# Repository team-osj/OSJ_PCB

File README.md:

# PCB Data for OSJ Project
## Specification
### Current Sensing Board
* Power Input - AC 90&#126;240V 50&#126;60HZ
* Main MCU - Atmel Atmega328 With Arduino Bootloader
* Current Sensor - Allegro ACS712 Hall Effect Sensor
* Communication - Nordic NRF24L01 2.4Ghz
### Gateway Board
* Power Input - DC 5V 2A
* Main MCU - Espressif ESP32-WROOM-32U
* Communication - WIFI 802.11 B,G,N   
                  Nordic NRF24L01 2.4Ghz
## Image
### Current Sensing Board TOP

### Current Sensing Board BOTTOM

### Gateway Board TOP

### Gateway Board BOTTOM

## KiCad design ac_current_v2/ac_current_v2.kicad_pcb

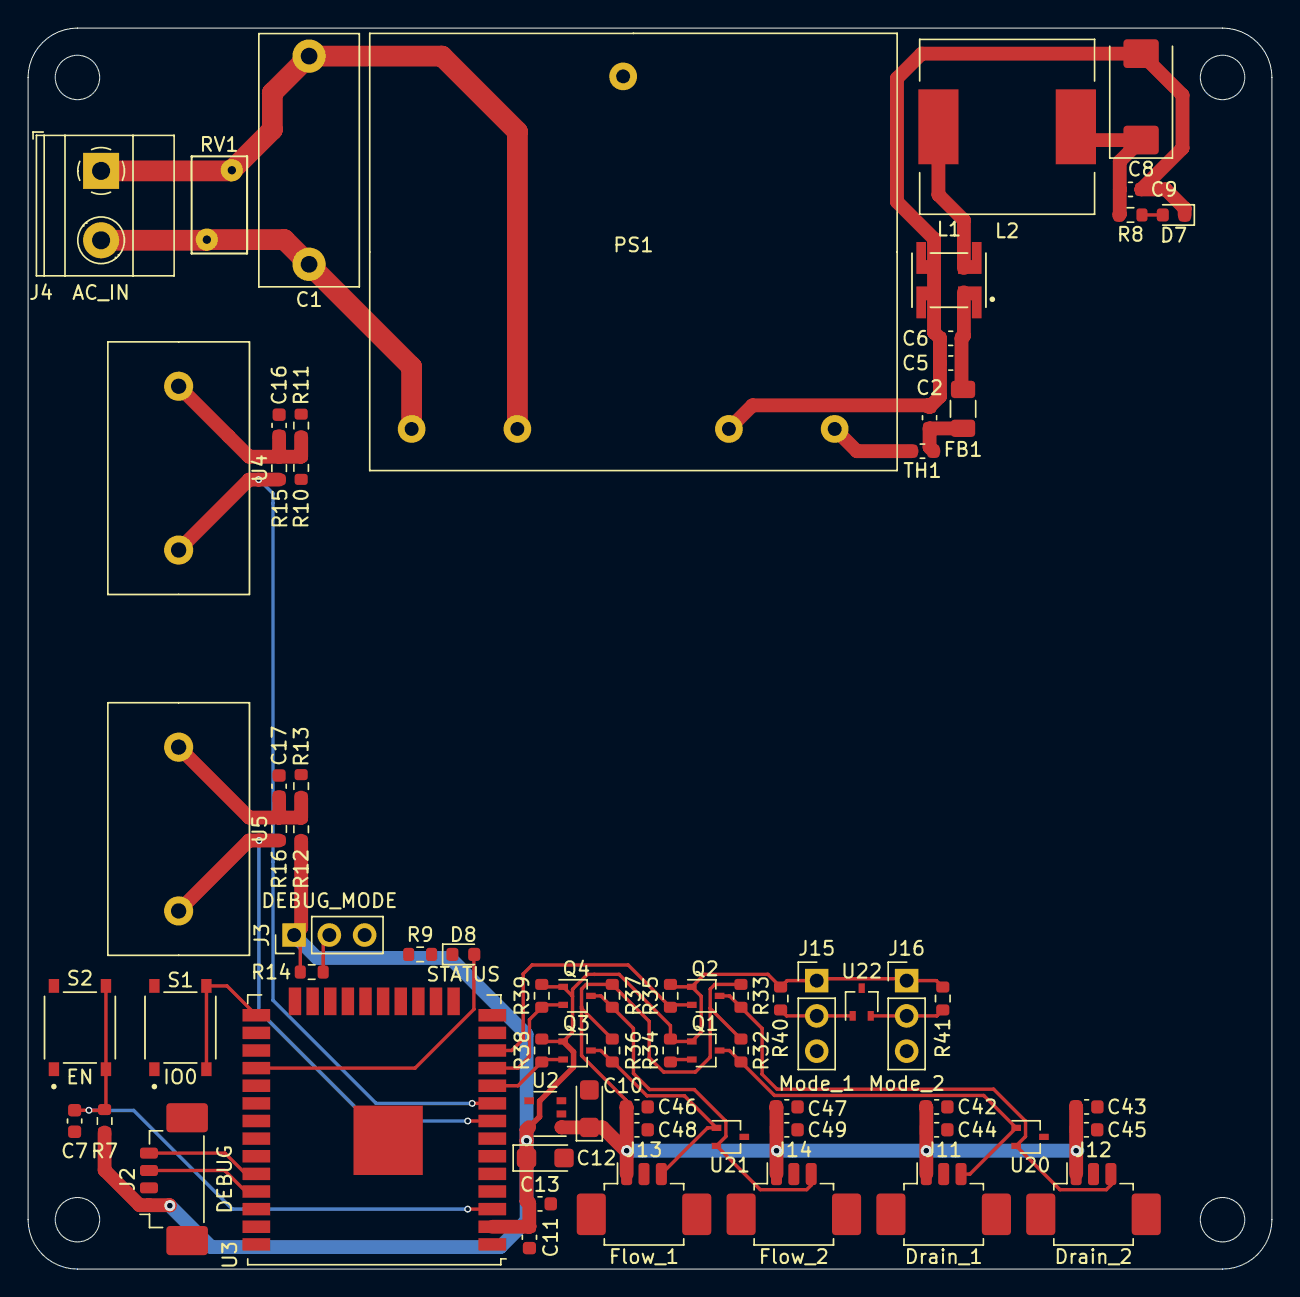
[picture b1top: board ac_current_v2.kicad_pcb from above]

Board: 2 copper layers, 89.6 x 89.4 mm, 75 parts (0 on the bottom side), 31 nets.

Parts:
C1: MPB224K27DZKN158G0; C_Rect_L18.0mm_W7.0mm_P15.00mm_FKS3_FKP3
C2: 10nf; C_0603_1608Metric
C5, C7, C9, C11: 100nf; C_0603_1608Metric
C6, C13, C16, C17, C42, C43, C46, C47: 10uf; C_0603_1608Metric
C8: 330uf; CP_EIA-7343-31_Kemet-D
C10, C12: 10uf; CP_EIA-3216-18_Kemet-A
C44, C45, C48, C49: 100uf; C_0603_1608Metric
D7: 5V; LED_0603_1608Metric
D8: STATUS; LED_0603_1608Metric
FB1: FBMH3216HM221NTV; Fuse_1206_3216Metric
H1, H2, H3, H4: MountingHole_Pad; MountingHole_3.2mm_M3
J2: DEBUG; Molex_PicoBlade_53398-0471_1x04-1MP_P1.25mm_Vertical
J3: DEBUG_MODE; PinHeader_1x03_P2.54mm_Vertical
J4: AC_IN; TerminalBlock_Phoenix_MKDS-1,5-2_1x02_P5.00mm_Horizontal
J11: Drain_1; Molex_PicoBlade_53261-0371_1x03-1MP_P1.25mm_Horizontal
J12: Drain_2; Molex_PicoBlade_53261-0371_1x03-1MP_P1.25mm_Horizontal
J13: Flow_1; Molex_PicoBlade_53261-0371_1x03-1MP_P1.25mm_Horizontal
J14: Flow_2; Molex_PicoBlade_53261-0371_1x03-1MP_P1.25mm_Horizontal
J15: Mode_1; PinHeader_1x03_P2.54mm_Vertical
J16: Mode_2; PinHeader_1x03_P2.54mm_Vertical
L1: DLW5ATN331MQ2L; FIL_DLW5ATN331MQ2L
L2: SCDS125T-220M-N; L_12x12mm_H6mm
PS1: GMS0505
Q1, Q2, Q3, Q4: 2N7002; SOT-323_SC-70
R7, R14, R32, R33, R34, R35, R36, R37, R38, R39, R40, R41: 10k; R_0603_1608Metric
R8: 330; R_0603_1608Metric
R9: 100; R_0603_1608Metric
R10, R11, R12, R13: 100k; R_0603_1608Metric
R15, R16: 33; R_0603_1608Metric
RV1: V07E230P; RV_Disc_D7mm_W4mm_P5mm
S1: IO0; SW_TS-1187A-B-A-B
S2: EN; SW_TS-1187A-B-A-B
TH1: BSMD0603-050-6V; Fuse_0603_1608Metric
U2: NCP603SN330; TSOP-5_1.65x3.05mm_P0.95mm
U3: ESP32-WROOM-32U
U4: CT_1; ZMCT103C
U5: CT_2; ZMCT103C
U20, U21, U22: TPD2E007; SOT-323_SC-70

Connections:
+3V3: C11.2, C12.1, C13.2, J2.1, J3.1, J15.1, J16.1, Q1.1, Q2.1, Q3.1, Q4.1, R7.1, R10.1, R12.1, R14.1, R34.2, R35.2, R38.2, R39.2, R40.2, R41.2, U2.5, U3.2
+5V: C8.1, C9.1, C10.1, C42.1, C43.1, C44.1, C45.1, C46.1, C47.1, C48.1, C49.1, J11.1, J12.1, J13.1, J14.1, L2.2, R8.1, R32.2, R33.2, R36.2, R37.2, U2.1
/CT_1: R15.2, U3.9, U4.1
/CT_2: R16.2, U3.8, U5.1
/Debug_SW: J3.2, R14.2, U3.36
/Drain_1: Q1.2, R34.1, U3.37
/Drain_2: Q2.2, R35.1, U3.12
/EN: C7.1, R7.2, S2.C, S2.D, U3.3
/Flow_1: Q3.2, R38.1, U3.10
/Flow_2: Q4.2, R39.1, U3.11
/IO0: S1.C, S1.D, U3.25
/RX_DEBUG: J2.4, U3.34
/STATUS: D8.2, U3.28
/Sheet65BE28DA/Drain_1: J11.3, Q1.3, R32.1, U20.1
/Sheet65BE28DA/Drain_2: J12.3, Q2.3, R33.1, U20.2
/Sheet65BE28DA/Flow_1: J13.3, Q3.3, R36.1, U21.1
/Sheet65BE28DA/Flow_2: J14.3, Q4.3, R37.1, U21.2
/Sheet65BE28DA/Mode_1: J15.2, R40.1, U22.1
/Sheet65BE28DA/Mode_2: J16.2, R41.1, U22.2
/TX_DEBUG: J2.3, U3.35
GND: C2.2, C5.2, C6.2, C7.2, C8.2, C9.2, C10.2, C11.1, C12.2, C13.1, C16.2, C17.2, C42.2, C43.2, C44.2, C45.2, C46.2, C47.2, C48.2, C49.2, D7.1, J2.2, J3.3, J11.2, J12.2, J13.2, J14.2, J15.3, J16.3, L1.3, L1.4, PS1.3, R9.1, R11.2, R13.2, S1.A, S1.B, S2.A, S2.B, U2.2, U3.1, U3.15, U3.38, U3.39, U20.3, U21.3, U22.3
LINE: C1.1, J4.2, PS1.1, RV1.1
NEUT: C1.2, J4.1, PS1.2, RV1.2
unnamed: C2.1, FB1.2, TH1.1
unnamed: C5.1, C6.1, FB1.1, L1.1
unnamed: C16.1, R10.2, R11.1, R15.1, U4.2
unnamed: C17.1, R12.2, R13.1, R16.1, U5.2
unnamed: D7.2, R8.2
unnamed: D8.1, R9.2
unnamed: L1.2, L2.1
unnamed: PS1.4, TH1.2

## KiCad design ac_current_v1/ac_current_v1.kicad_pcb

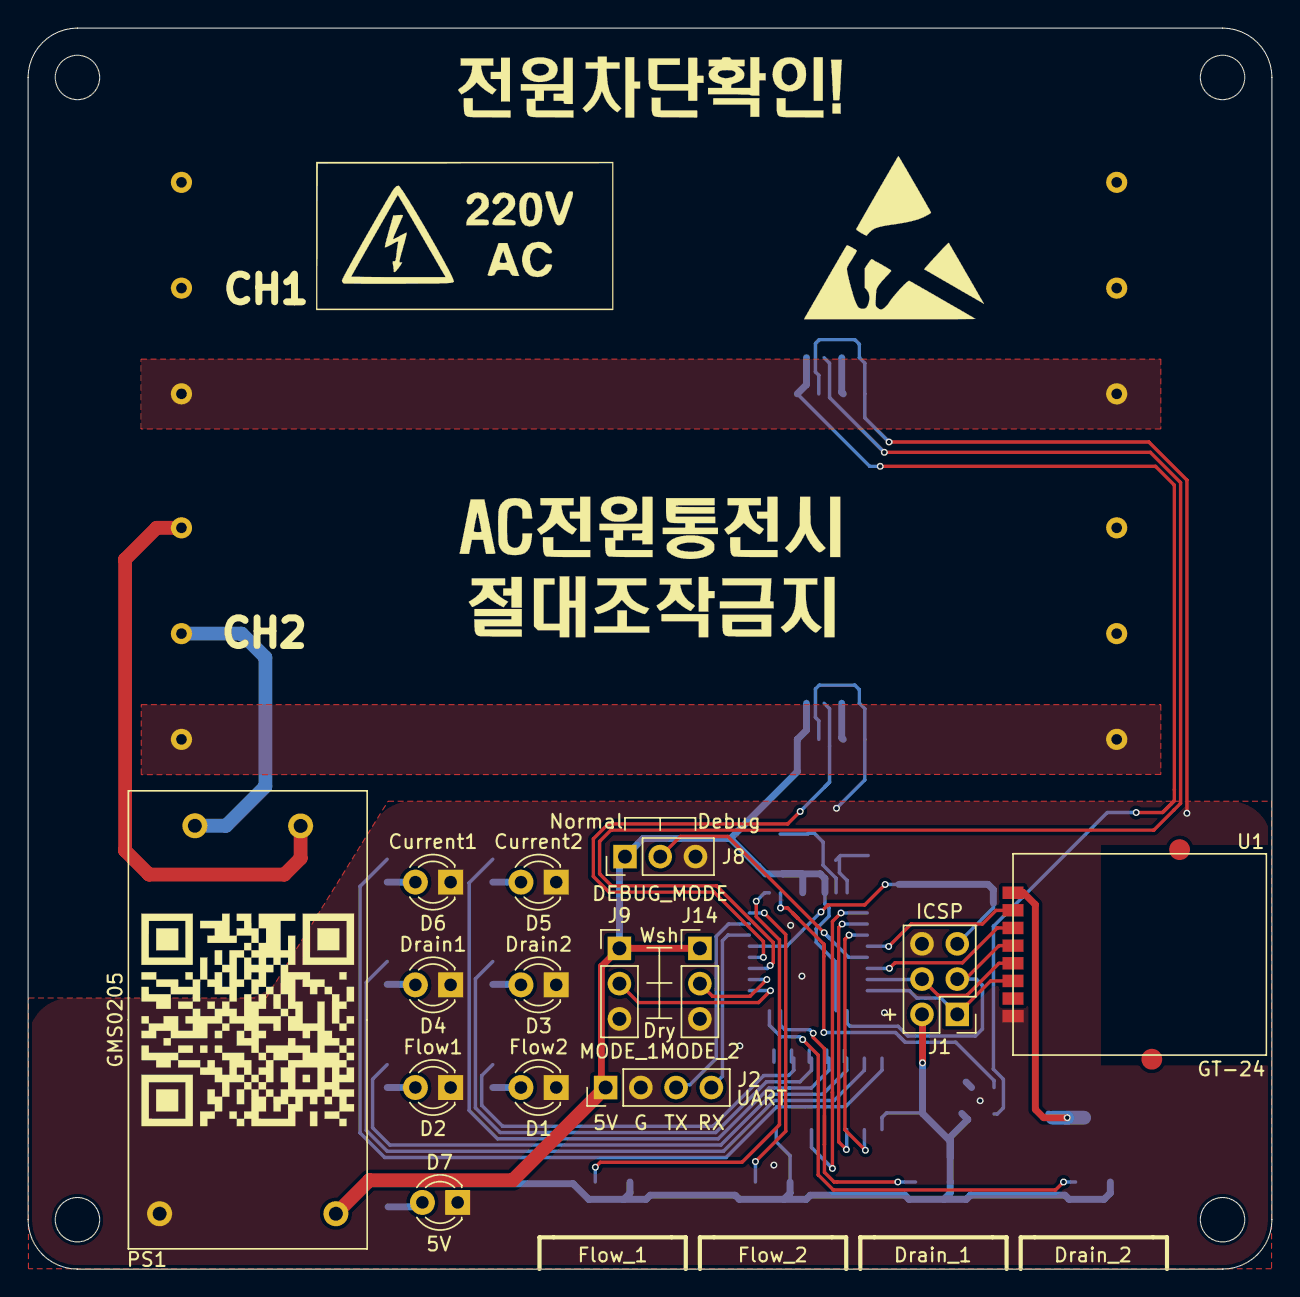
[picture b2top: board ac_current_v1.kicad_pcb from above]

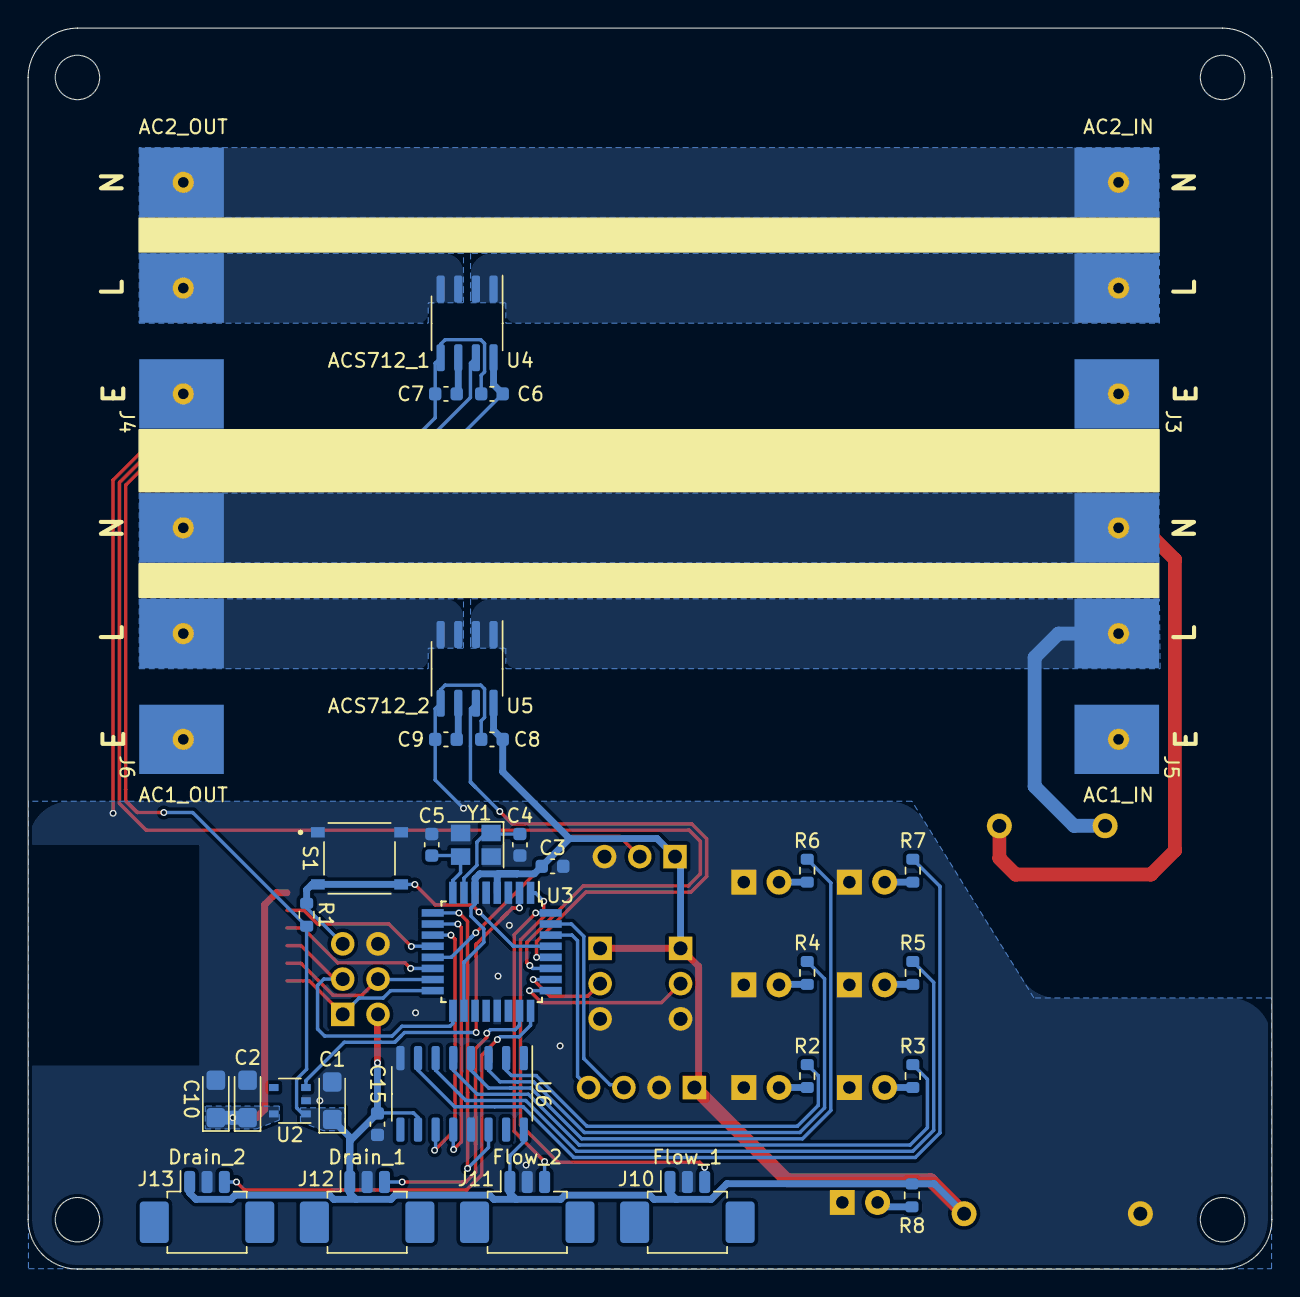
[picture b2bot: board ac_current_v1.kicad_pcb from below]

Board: 2 copper layers, 89.6 x 89.4 mm, 52 parts (34 on the bottom side), 49 nets.

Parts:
C1, C2, C10: 10uf; CP_EIA-3216-18_Kemet-A
C3, C6, C8, C15: 100nf; C_0603_1608Metric
C4, C5: 22pf; C_0603_1608Metric
C7, C9: 1nf; C_0603_1608Metric
D1: Flow2; LED_D3.0mm
D2: Flow1; LED_D3.0mm
D3: Drain2; LED_D3.0mm
D4: Drain1; LED_D3.0mm
D5: Current2; LED_D3.0mm
D6: Current1; LED_D3.0mm
D7: 5V; LED_D3.0mm
H1, H2, H3, H4: MountingHole_Pad; MountingHole_3.2mm_M3
J1: ICSP; PinHeader_2x03_P2.54mm_Vertical
J2: UART; PinHeader_1x04_P2.54mm_Vertical
J3: AC2_IN; SMD_762
J4: AC2_OUT; SMD_762
J5: AC1_IN; SMD_762
J6: AC1_OUT; SMD_762
J8: DEBUG_MODE; PinHeader_1x03_P2.54mm_Vertical
J9: MODE_1; PinHeader_1x03_P2.54mm_Vertical
J10: Flow_1; Molex_PicoBlade_53261-0371_1x03-1MP_P1.25mm_Horizontal
J11: Flow_2; Molex_PicoBlade_53261-0371_1x03-1MP_P1.25mm_Horizontal
J12: Drain_1; Molex_PicoBlade_53261-0371_1x03-1MP_P1.25mm_Horizontal
J13: Drain_2; Molex_PicoBlade_53261-0371_1x03-1MP_P1.25mm_Horizontal
J14: MODE_2; PinHeader_1x03_P2.54mm_Vertical
PS1: GMS0205
R1: 10k; R_0603_1608Metric
R2, R3, R4, R5, R6, R7, R8: 330; R_0603_1608Metric
S1: RST; SW_TS-1187A-B-A-B
U1: GT-24; nrf24l01 smd
U2: NCP603SN330; TSOP-5_1.65x3.05mm_P0.95mm
U3: ATmega328P-AU; TQFP-32_7x7mm_P0.8mm
U4: ACS712_1; SOIC-8_3.9x4.9mm_P1.27mm
U5: ACS712_2; SOIC-8_3.9x4.9mm_P1.27mm
U6: 74HC595; SO-16_3.9x9.9mm_P1.27mm
Y1: 16Mhz; Crystal_SMD_3225-4Pin_3.2x2.5mm

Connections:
+3V3: C2.1, C10.1, U1.1, U2.5
+5V: C1.1, C3.2, C6.1, C8.1, C15.1, J1.2, J2.1, J8.1, J9.1, J10.1, J11.1, J12.1, J13.1, J14.1, PS1.4, R1.2, R8.1, U2.1, U3.4, U3.6, U3.18, U4.8, U5.8, U6.10, U6.16
/A0: J12.3, U3.23
/A1: J13.3, U3.24
/A2: J9.2, U3.25
/A3: J14.2, U3.26
/A4: U3.27, U4.7
/A5: U3.28, U5.7
/D2: J11.3, U3.32
/D3: J10.3, U3.1
/D4: U2.3, U3.2
/D5: U3.9, U6.14
/D6: U3.10, U6.12
/D7: U3.11, U6.11
/D8: U1.2, U3.12
/D9: J8.2, U3.13
/D10: U1.3, U3.14
/D11: J1.4, U1.5, U3.15
/D12: J1.1, U1.6, U3.16
/D13: J1.3, U1.4, U3.17
/RST: J1.5, R1.1, S1.C, S1.D, U3.29
/RX: J2.4, U3.30
/TX: J2.3, U3.31
GND: C1.2, C2.2, C3.1, C4.1, C5.1, C6.2, C7.2, C8.2, C9.2, C10.2, C15.2, D1.1, D2.1, D3.1, D4.1, D5.1, D6.1, D7.1, J1.6, J2.2, J8.3, J9.3, J10.2, J11.2, J12.2, J13.2, J14.3, PS1.3, S1.A, S1.B, U1.8, U2.2, U3.3, U3.5, U3.21, U4.5, U5.5, U6.8, U6.13, Y1.2, Y1.4
GND1: J3.1, J4.1
GND2: J5.1, J6.1
LINE: J5.3, J6.3, PS1.1
NEUT: J5.2, PS1.2, U5.1, U5.2
unnamed: C4.2, U3.7, Y1.1
unnamed: C5.2, U3.8, Y1.3
unnamed: C7.1, U4.6
unnamed: C9.1, U5.6
unnamed: D1.2, R2.2
unnamed: D2.2, R3.2
unnamed: D3.2, R4.2
unnamed: D4.2, R5.2
unnamed: D5.2, R6.2
unnamed: D6.2, R7.2
unnamed: D7.2, R8.2
unnamed: J3.2, U4.1, U4.2
unnamed: J3.3, J4.3
unnamed: J4.2, U4.3, U4.4
unnamed: J6.2, U5.3, U5.4
unnamed: R2.1, U6.2
unnamed: R3.1, U6.5
unnamed: R4.1, U6.3
unnamed: R5.1, U6.6
unnamed: R6.1, U6.4
unnamed: R7.1, U6.7

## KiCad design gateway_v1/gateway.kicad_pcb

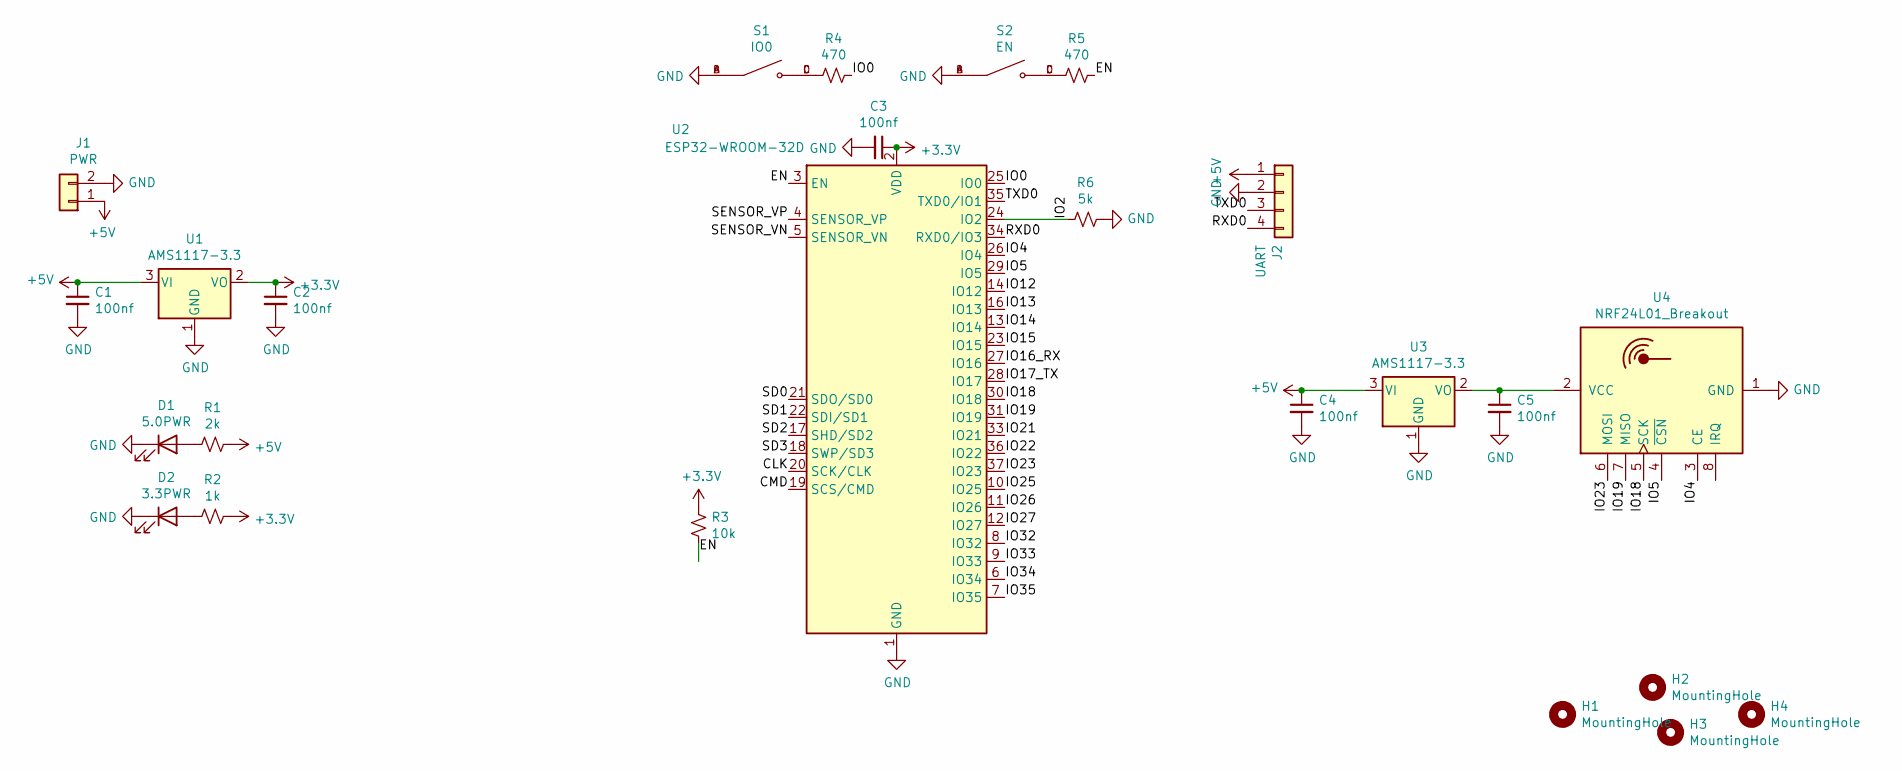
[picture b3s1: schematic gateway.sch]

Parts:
C1, C2, C3, C4, C5: 100nf; C_0603_1608Metric
D1: 5.0PWR; LED_0603_1608Metric
D2: 3.3PWR; LED_0603_1608Metric
H1, H2: MountingHole; MountingHole_4.3mm_M4
H3, H4: MountingHole; MountingHole_3.2mm_M3
J1: PWR; PinHeader_1x02_P2.54mm_Vertical
J2: UART; PinHeader_1x04_P2.54mm_Vertical
R1: 2k; R_0603_1608Metric
R2: 1k; R_0603_1608Metric
R3: 10k; R_0603_1608Metric
R4, R5: 470; R_0603_1608Metric
R6: 5k; R_0603_1608Metric
S1: IO0; SW_TS-1187A-B-A-B; PARTREV A0
S2: EN; SW_TS-1187A-B-A-B; PARTREV A0
U1, U3: AMS1117-3.3; SOT-223-3_TabPin2
U2: ESP32-WROOM-32D; ESP32-WROOM-32U
U4: NRF24L01_Breakout; NRF24L01_PA_LNA

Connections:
+3V3: C2.1, C3.1, R2.1, R3.1, U1.2 (VO), U2.2 (VDD)
+5V: C1.1, C4.1, J1.1, J2.1, R1.1, U1.3 (VI), U3.3 (VI)
/CLK: U2.20 (SCK/CLK)
/CMD: U2.19 (SCS/CMD)
/EN: R3.2, R5.1, U2.3 (EN)
/IO0: R4.1, U2.25 (IO0)
/IO2: R6.2, U2.24 (IO2)
/IO4: U2.26 (IO4), U4.3 (CE)
/IO5: U2.29 (IO5), U4.4 (~CSN)
/IO12: U2.14 (IO12)
/IO13: U2.16 (IO13)
/IO14: U2.13 (IO14)
/IO15: U2.23 (IO15)
/IO16_RX: U2.27 (IO16)
/IO17_TX: U2.28 (IO17)
/IO18: U2.30 (IO18), U4.5 (SCK)
/IO19: U2.31 (IO19), U4.7 (MISO)
/IO21: U2.33 (IO21)
/IO22: U2.36 (IO22)
/IO23: U2.37 (IO23), U4.6 (MOSI)
/IO25: U2.10 (IO25)
/IO26: U2.11 (IO26)
/IO27: U2.12 (IO27)
/IO32: U2.8 (IO32)
/IO33: U2.9 (IO33)
/IO34: U2.6 (IO34)
/IO35: U2.7 (IO35)
/RXD0: J2.4, U2.34 (RXD0/IO3)
/SD0: U2.21 (SDO/SD0)
/SD1: U2.22 (SDI/SD1)
/SD2: U2.17 (SHD/SD2)
/SD3: U2.18 (SWP/SD3)
/SENSOR_VN: U2.5 (SENSOR_VN)
/SENSOR_VP: U2.4 (SENSOR_VP)
/TXD0: J2.3, U2.35 (TXD0/IO1)
GND: C1.2, C2.2, C3.2, C4.2, C5.2, D1.1 (K), D2.1 (K), J1.2, J2.2, R6.1, S1.A, S1.B, S2.A, S2.B, U1.1 (GND), U2.1 (GND), U2.15 (GND), U2.38 (GND), U2.39 (GND), U3.1 (GND), U4.1 (GND)
unnamed: C5.1, U3.2 (VO), U4.2 (VCC)
unnamed: D1.2 (A), R1.2
unnamed: D2.2 (A), R2.2
unnamed: R4.2, S1.C, S1.D
unnamed: R5.2, S2.C, S2.D

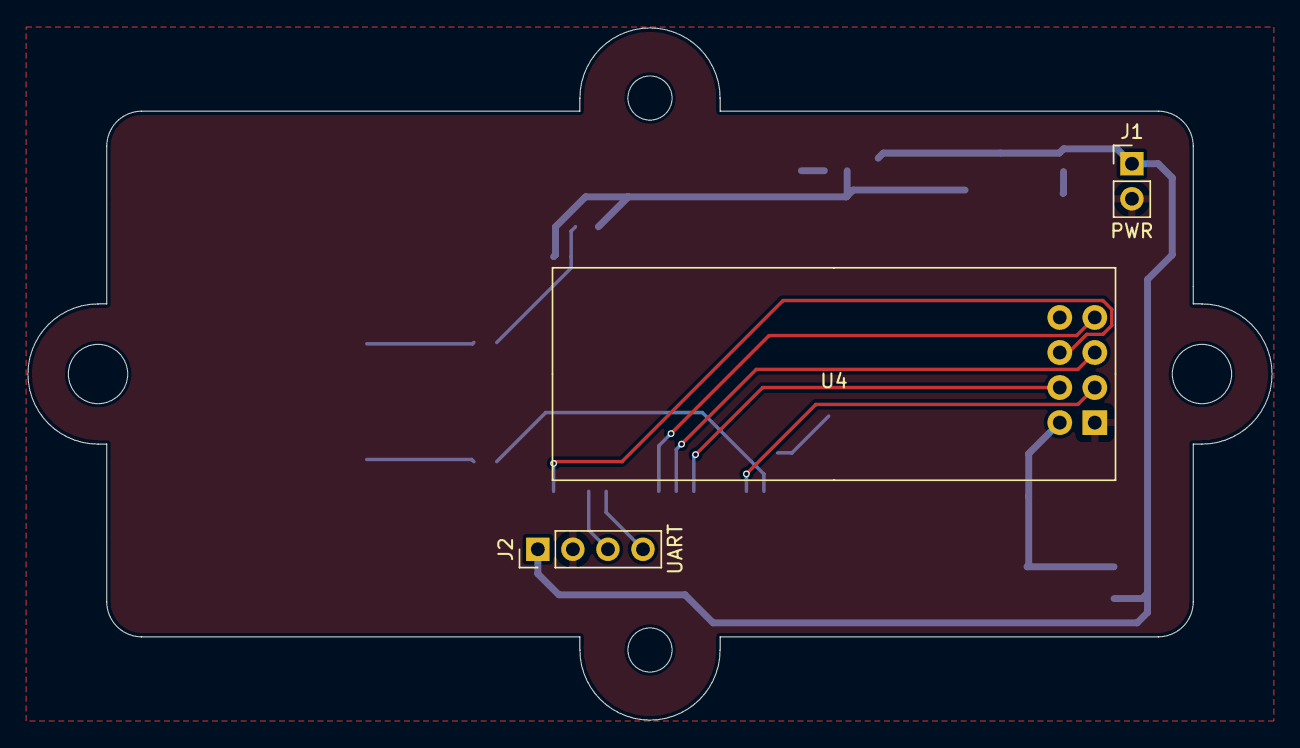
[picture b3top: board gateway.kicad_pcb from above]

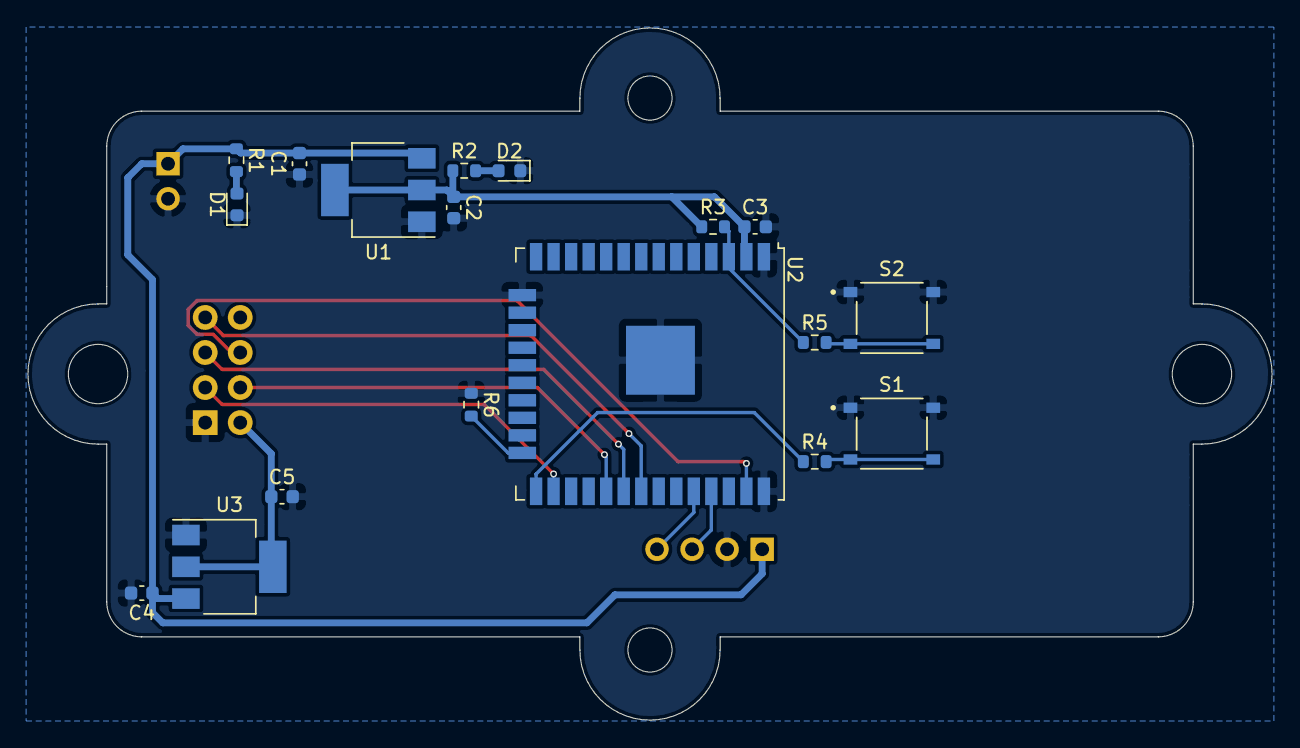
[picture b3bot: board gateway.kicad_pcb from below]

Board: 2 copper layers, 90.2 x 50.2 mm, 25 parts (18 on the bottom side), 18 nets.

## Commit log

2022-12-10 PCB File update
2022-12-10 Image update
2022-12-10 Update image
2022-12-10 Update text
2022-12-10 add specification
2022-12-10 update specification
2022-12-10 Tilde
2022-12-25 Schematic update
2023-02-26 PCB Update(Added Sensor)
2024-01-01 PCB Update
2024-01-01 Readme 이미지 업데이트
2024-01-01 Board Assembly 이미지 추가
